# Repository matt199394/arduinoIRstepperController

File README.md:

I had the problem to remotely controll the volume of my home-built audio amplifier. For this purpose I created a circuit that allows me to control a stepper motor connected to the amplifier's potentiometer. The stepper motor can be controlled either using the remote control or the rotary encoder. I have to admit it works pretty well :)
I hope it's useful for someone!

Link to a brief video demonstration https://www.youtube.com/watch?v=Ed6FCPk_Rfs

Code update: add timer to disable stepper motor after 5 seconds if no change in stepper position

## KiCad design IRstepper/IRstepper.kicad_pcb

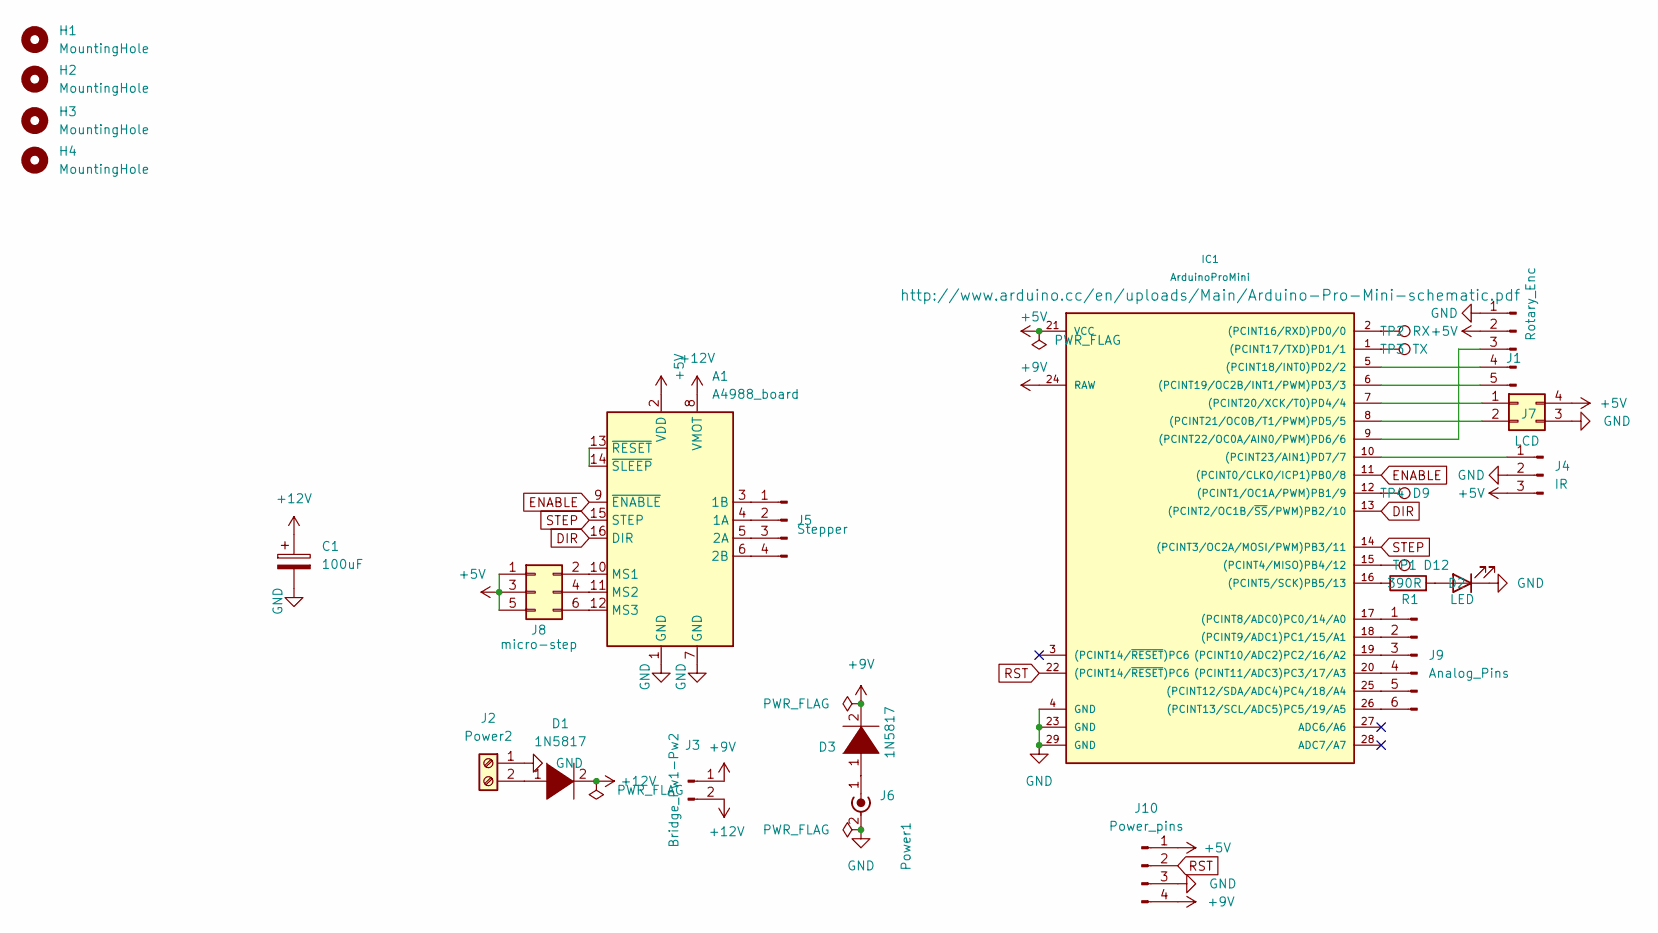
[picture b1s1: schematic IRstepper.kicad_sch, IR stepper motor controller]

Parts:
A1: A4988_board; Pololu_Breakout-16_15.2x20.3mm
C1: 100uF; CP_Radial_D8.0mm_P3.50mm
D1, D3: 1N5817; D_A-405_P7.62mm_Horizontal
D2: LED; LED_D3.0mm
H1, H2, H3, H4: MountingHole; MountingHole_3.7mm_Pad_TopBottom
IC1: ArduinoProMini; pro_mini
J1: Rotary_Enc; PinHeader_1x05_P2.54mm_Vertical
J2: Power2; TerminalBlock_Phoenix_PT-1,5-2-5.0-H_1x02_P5.00mm_Horizontal
J3: Bridge_Pw1-Pw2; PinHeader_1x02_P2.54mm_Vertical
J4: IR; PinHeader_1x03_P2.54mm_Vertical
J5: Stepper; PinHeader_1x04_P2.54mm_Vertical
J6: Power1; BarrelJack_Horizontal
J7: LCD; PinHeader_2x02_P2.54mm_Vertical
J8: micro-step; PinHeader_2x03_P2.54mm_Vertical
J9: Analog_Pins; PinHeader_1x06_P2.54mm_Vertical
J10: Power_pins; PinHeader_1x04_P2.54mm_Vertical
R1: 390R; R_Axial_DIN0207_L6.3mm_D2.5mm_P7.62mm_Horizontal
TP1: D12; TestPoint_Pad_D1.5mm
TP2: RX; TestPoint_Pad_D1.5mm
TP3: TX; TestPoint_Pad_D1.5mm
TP4: D9; TestPoint_Pad_D1.5mm

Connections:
+5V: A1.2 (VDD), IC1.21 (VCC), J1.2, J4.3, J7.4, J8.1, J8.3, J8.5, J10.1
+9V: D3.2 (A), IC1.24 (RAW), J3.1, J10.4
+12V: A1.8 (VMOT), C1.1, D1.2 (A), J3.2
DIR: A1.16 (DIR), IC1.13 ((PCINT2/OC1B/~SS/PWM)PB2/10)
ENABLE: A1.9 (~ENABLE), IC1.11 ((PCINT0/CLKO/ICP1)PB0/8)
GND: A1.1 (GND), A1.7 (GND), C1.2, D2.1 (K), IC1.4 (GND), IC1.23 (GND), IC1.29 (GND), J1.1, J2.1, J4.2, J6.2 (Ext), J6.3, J7.3, J10.3
unnamed: A1.3 (1B), J5.1
unnamed: A1.4 (1A), J5.2
unnamed: A1.5 (2A), J5.3
unnamed: A1.6 (2B), J5.4
unnamed: A1.10 (MS1), J8.2
unnamed: A1.11 (MS2), J8.4
unnamed: A1.12 (MS3), J8.6
unnamed: A1.13 (~RESET), A1.14 (~SLEEP)
unnamed: D1.1 (K), J2.2
unnamed: D2.2 (A), R1.2
unnamed: D3.1 (K), J6.1 (In)
unnamed: IC1.1 ((PCINT17/TXD)PD1/1), TP3.1
unnamed: IC1.2 ((PCINT16/RXD)PD0/0), TP2.1
unnamed: IC1.5 ((PCINT18/INT0)PD2/2), J1.4
unnamed: IC1.6 ((PCINT19/OC2B/INT1/PWM)PD3/3), J1.5
unnamed: IC1.7 ((PCINT20/XCK/T0)PD4/4), J7.1
unnamed: IC1.8 ((PCINT21/OC0B/T1/PWM)PD5/5), J7.2
unnamed: IC1.9 ((PCINT22/OC0A/AIN0/PWM)PD6/6), J1.3
unnamed: IC1.10 ((PCINT23/AIN1)PD7/7), J4.1
unnamed: IC1.12 ((PCINT1/OC1A/PWM)PB1/9), TP4.1
unnamed: IC1.15 ((PCINT4/MISO)PB4/12), TP1.1
unnamed: IC1.16 ((PCINT5/SCK)PB5/13), R1.1
unnamed: IC1.17 ((PCINT8/ADC0)PC0/14/A0), J9.1
unnamed: IC1.18 ((PCINT9/ADC1)PC1/15/A1), J9.2
unnamed: IC1.19 ((PCINT10/ADC2)PC2/16/A2), J9.3
unnamed: IC1.20 ((PCINT11/ADC3)PC3/17/A3), J9.4
unnamed: IC1.25 ((PCINT12/SDA/ADC4)PC4/18/A4), J9.5
unnamed: IC1.26 ((PCINT13/SCL/ADC5)PC5/19/A5), J9.6
RST: IC1.22 ((PCINT14/~RESET)PC6), J10.2
STEP: A1.15 (STEP), IC1.14 ((PCINT3/OC2A/MOSI/PWM)PB3/11)

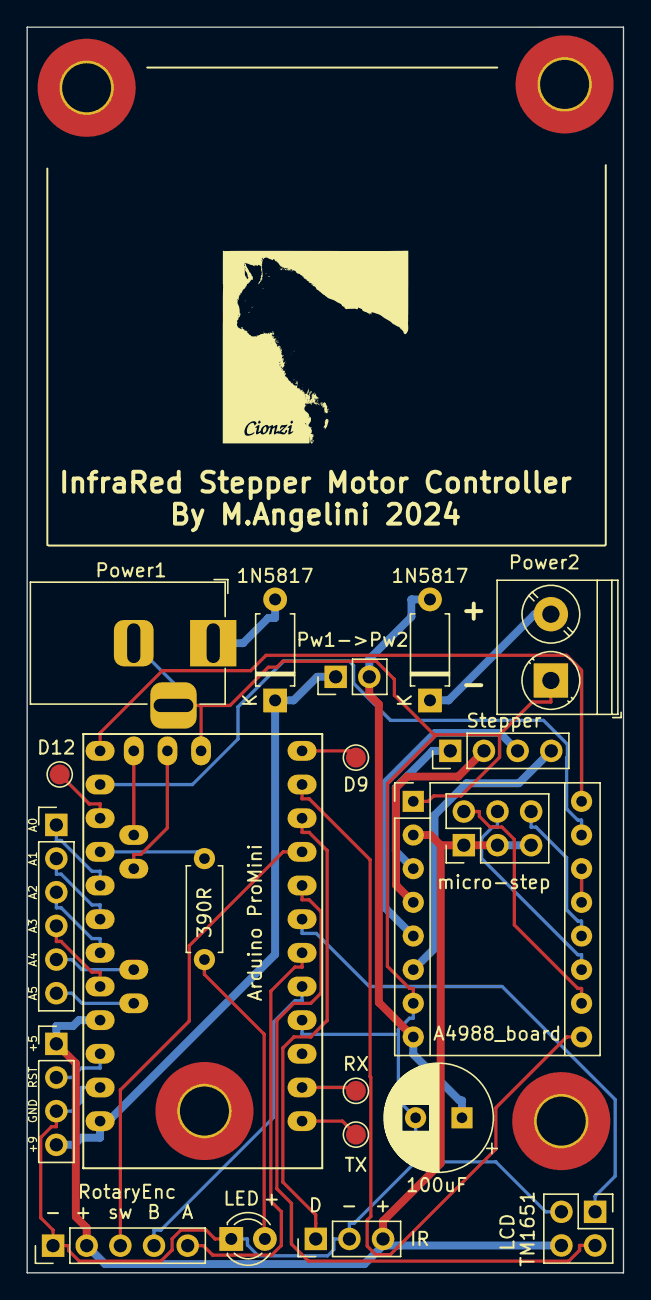
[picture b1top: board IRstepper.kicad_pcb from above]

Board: 2 copper layers, 45.0 x 94.0 mm, 26 parts (0 on the bottom side), 36 nets.

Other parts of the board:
 : LOGO; cionzi

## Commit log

2024-06-28 Update arduinoIRstepper.ino
    Add timer to disable stepper motor after 5 seconds if no change in stepper position
